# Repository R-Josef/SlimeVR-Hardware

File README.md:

# SlimeVR-Hardware

This is a SlimeVR hardware project, including a PCB file and case models.

## Feature

* Using modules instead of SMD, the parts are consistent with the [schematics of the official document](https://docs.slimevr.dev/diy/tracker-schematics.html)
* The wiring method is consistent with the schematics of the official document too, no need to change the pin definition.
* Battery sense
* Charge diodes
* Auxiliary tracker connector (optional)

## Build your own trackers

### Prepare the parts

First, prepare the following materials:

| Designator | Materials                                      | Quantity | Comment                                               |
| ---------- | ---------------------------------------------- | -------- | ----------------------------------------------------- |
| U1         | ESP8266-D1-Mini                                | 1        | Also called WeMos D1 Mini, Type-C is recommended      |
| U2         | BNO08X                                         | 1        | IMU, BNO085/BNO080                                    |
| U3         | TP4056                                         | 1        | TP4056, Type-C is recommended                         |
| D1, D2     | 1N5817                                         | 2        | Charge diodes                                         |
| R1         | 180k 1/4W resistor                             | 1        | Battery sense                                         |
| SM1        | MSK-12D19 (1P2T)                               | 1        | Toggle Switch                                         |
| BT1        | Molex PicoBlade connector 1x2p 1.25mm vertical | 1        | This is a common connector type for lithium batteries |
|            | 3.7v lithium battery                           | 1        | 10*25*40mm (102540) is recommended                    |
| J1         | Molex PicoBlade connector 1x5p 1.25mm vertical | 1        | Auxiliary tracker connector (this is an optional)     |
| JP1        | PinHeader 1x2p 1.27mm vertical                 | 1        | Pinheader for jumper (this is an optional)            |

Then you need to download the [Gerber.zip](https://github.com/R-Josef/SlimeVR-Hardware/releases/latest/download/Gerber.zip) file, provide this file to the PCB manufacturer to make your boards.

Finally, download the [Case.stl](https://github.com/R-Josef/SlimeVR-Hardware/releases/latest/download/Case.stl) file and [Lip.stl](https://github.com/R-Josef/SlimeVR-Hardware/releases/latest/download/Lip.stl) file and use it for 3d printing, you will get cases.

### Soldering

Solder the parts that need to be soldered to the PCB, Your board should now look like this:

You can now connect the D1 Mini to your computer with a USB cable, and then burn the firmware. If everything is ok, you can plug the lithium battery into the connector:

Last step, put the tracker in the box and snap the lid on, you may need Hot-melt adhesive to hold it in place. Now your tracker is ready, enjoy it!

### About auxiliary tracker

If you need to connect a auxiliary tracker, you should use this case with a hole: [Case-AuxHole.stl](https://github.com/R-Josef/SlimeVR-Hardware/releases/latest/download/Case-AuxHole.stl) [Lip-AuxHole.stl](https://github.com/R-Josef/SlimeVR-Hardware/releases/latest/download/Lip-AuxHole.stl) , the extra hole is used to pass the connecting wire of the auxiliary tracker. In order to use the auxiliary tracker, you need also to solder J1 and JP1 to the PCB, then prepare a jumper cap, and insert the jumper cap on JP1.

## Configuring the Firmware

You can clone or download the firmware on [official frimware repo](https://github.com/SlimeVR/SlimeVR-Tracker-ESP) , if you don't use auxiliary tracker, just make the following changes in `defines.h` :

```c
#define BOARD BOARD_WEMOSD1MINI
#define IMU_ROTATION DEG_180
```

If you use auxiliary tracker, then also need to make the following changes in `defines.h` :

```c
#define SECOND_IMU BNO085
#define SECOND_IMU_ROTATION DEG_0
```

For other settings, please follow the [official documentation](https://docs.slimevr.dev/).

## View or modify source files

The SlimeVR-PCB folder is the KiCad project folder, while the SlimeVR-Case folder has the FreeCAD model files for the case and lid.

## preview

### PCB

### Case

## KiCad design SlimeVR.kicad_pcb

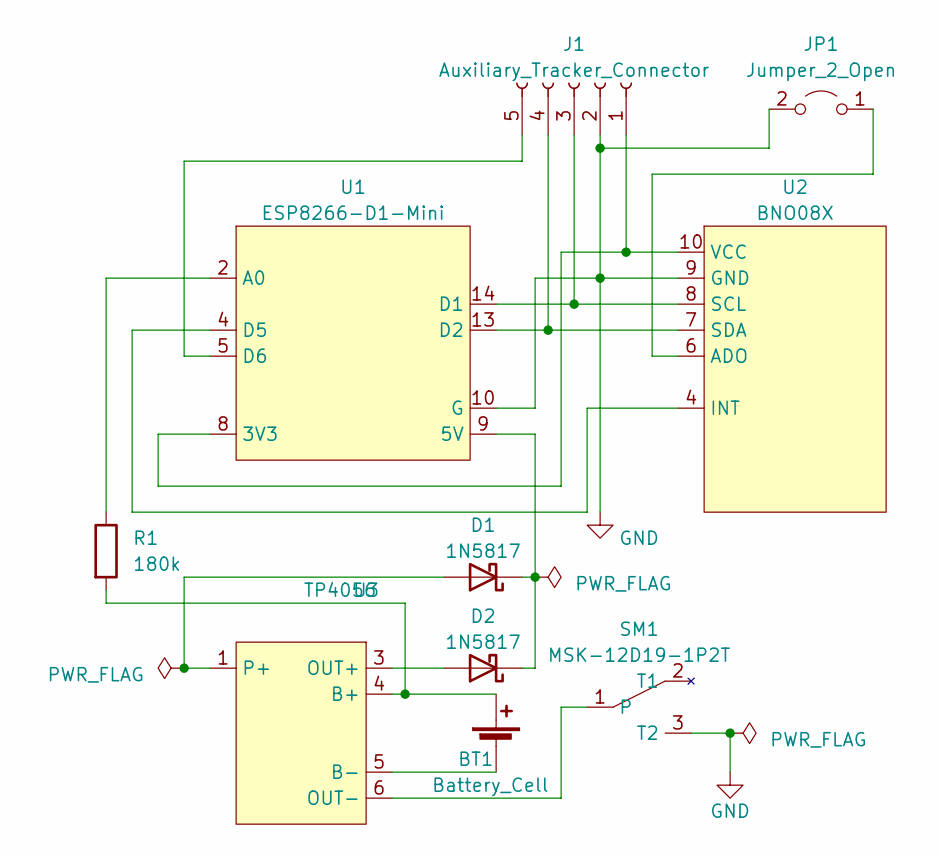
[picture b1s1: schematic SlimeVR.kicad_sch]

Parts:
BT1: Battery_Cell; Molex_PicoBlade_53047-0210_1x02_P1.25mm_Vertical
D1, D2: 1N5817; D_DO-41_SOD81_P10.16mm_Horizontal
J1: Auxiliary_Tracker_Connector; Molex_PicoBlade_53047-0510_1x05_P1.25mm_Vertical
JP1: Jumper_2_Open; PinHeader_1x02_P1.27mm_Vertical
R1: 180k; R_Axial_DIN0207_L6.3mm_D2.5mm_P10.16mm_Horizontal
SM1: MSK-12D19-1P2T
U1: ESP8266-D1-Mini; WEMOS_D1_mini_light
U2: BNO08X
U3: TP4056; TP4056_MAO

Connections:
GND: J1.2, JP1.2 (B), SM1.3 (T2), U1.10 (G), U2.9 (GND)
unnamed: BT1.1 (+), R1.2, U3.4 (B+)
unnamed: BT1.2 (-), U3.5 (B-)
unnamed: D1.2 (A), U3.1 (P+)
unnamed: D1.1 (K), D2.1 (K), U1.9 (5V)
unnamed: D2.2 (A), U3.3 (OUT+)
unnamed: J1.1, U1.8 (3V3), U2.10 (VCC)
unnamed: J1.3, U1.14 (D1), U2.8 (SCL)
unnamed: J1.4, U1.13 (D2), U2.7 (SDA)
unnamed: J1.5, U1.5 (D6)
unnamed: JP1.1 (A), U2.6 (ADO)
unnamed: SM1.1, U3.6 (OUT-)
unnamed: R1.1, U1.2 (A0)
unnamed: U1.4 (D5), U2.4 (INT)

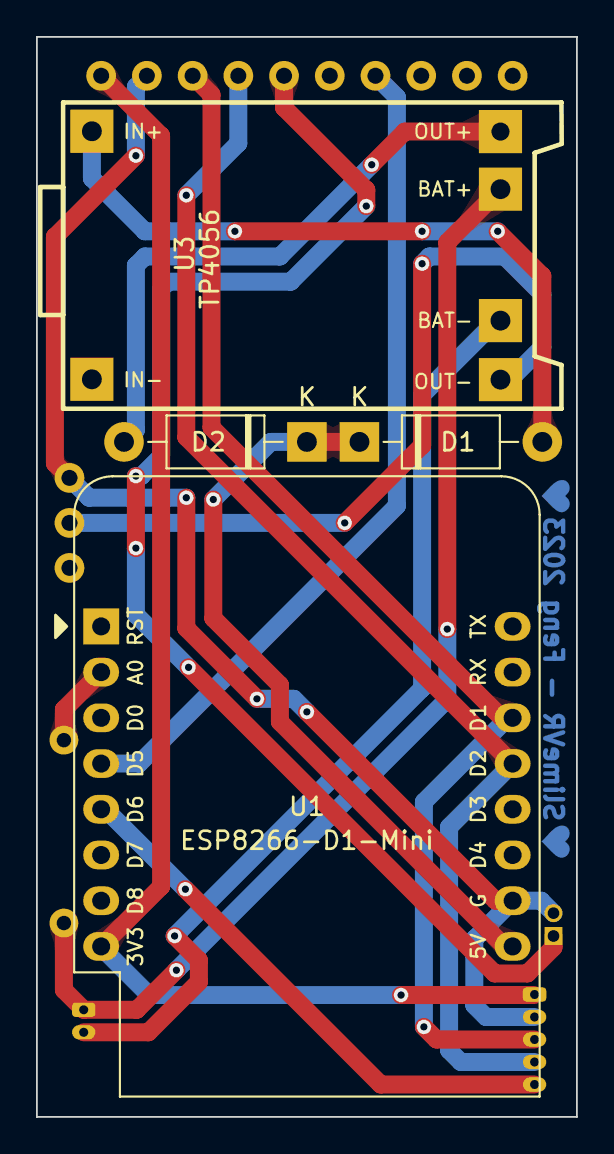
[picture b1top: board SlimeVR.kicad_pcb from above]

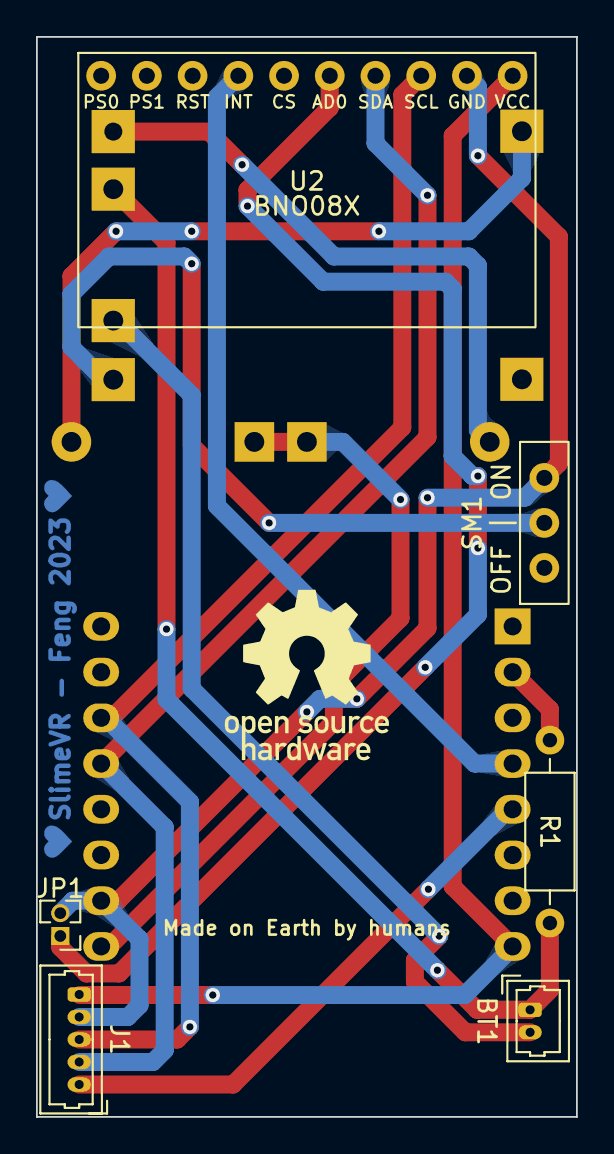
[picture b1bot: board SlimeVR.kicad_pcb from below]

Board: 2 copper layers, 30.0 x 60.0 mm, 10 parts (6 on the bottom side), 14 nets.

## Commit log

2023-02-19 Add .gitignore
2023-02-19 Add kicad project files
2023-02-19 Change gerber export rules
2023-02-22 Change file structure
2023-02-22 Add FreeCAD case files
2023-02-25 Add README.md
2023-04-18 Fix hole position
2023-04-18 Add a case version with hole to let aux traker wire go out side
